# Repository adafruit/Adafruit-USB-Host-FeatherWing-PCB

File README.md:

## Adafruit USB Host FeatherWing with MAX3421E PCB

<a href="http://www.adafruit.com/products/5858"><br/>
Click here to purchase one from the Adafruit shop</a>

PCB files for the Adafruit USB Host FeatherWing with MAX3421E. 

Format is EagleCAD schematic and board layout
* https://www.adafruit.com/product/5858

### Description

Lots of microcontrollers these days have USB ports on them, to program or debug, act like a keyboard or disk drive, or simply send data between a computer and your firmware. But did you know that you can also add a USB Host port? That means that your microcontroller project can have a keyboard or mouse or disk drive plugged into it - which opens up a huge ecosystem of common off-the-shelf devices that you can now integrate. The Adafruit USB Host FeatherWing makes it easy to add USB Host support, especially now that TinyUSB supports it in the Arduino library as a 'native' interface for host support. 

This Wing uses the MAX3421E - a tried and true USB Host chip. It uses SPI plus an IRQ pin to send data to just about any USB device. Note that because the chip is older, and you're limited to the SPI port speed, you're not going to get blazing 480Mbps high speed data transfer. But for basic HID interfacing, or even reading/writing to a Mass Storage device, it does work quite well. There's a famous USB Host Library that can be used, and it's specialty is AVR support, but also seems to support nRF52 and ESP32. We personally recommend using the TinyUSB Arduino library - however the trade-off is that the chip must have TinyUSB support already which means it's great for RP2040, ESP32-S2 or S3, nRF52840, SAMD21/51 chips. Between the two libraries, just make sure your desired Feather mainboard is supported before purchasing! 

Next to the MAX3421E we have a 5V 1A booster with 500mA fuse, which can provide a nice clean 5V from the USB or Battery power supply. An enable pin is available to power cycle when desired.

Comes as an assembled Wing with some header. Solder on the header and plug into a Feather Mainboard to expand it's capabilities! Don't forget, you need driver support for the MAX3421E (see above for chips that are known working) and unless you're using a generic mouse, keyboard, CDC serial or USB mass storage device you will also need a USB driver that knows how to talk to the device - and writing a driver is non-trivial.

### License

Adafruit invests time and resources providing this open source design, please support Adafruit and open-source hardware by purchasing products from [Adafruit](https://www.adafruit.com)!

Designed by Limor Fried/Ladyada for Adafruit Industries.

Creative Commons Attribution/Share-Alike, all text above must be included in any redistribution. 
See license.txt for additional details.

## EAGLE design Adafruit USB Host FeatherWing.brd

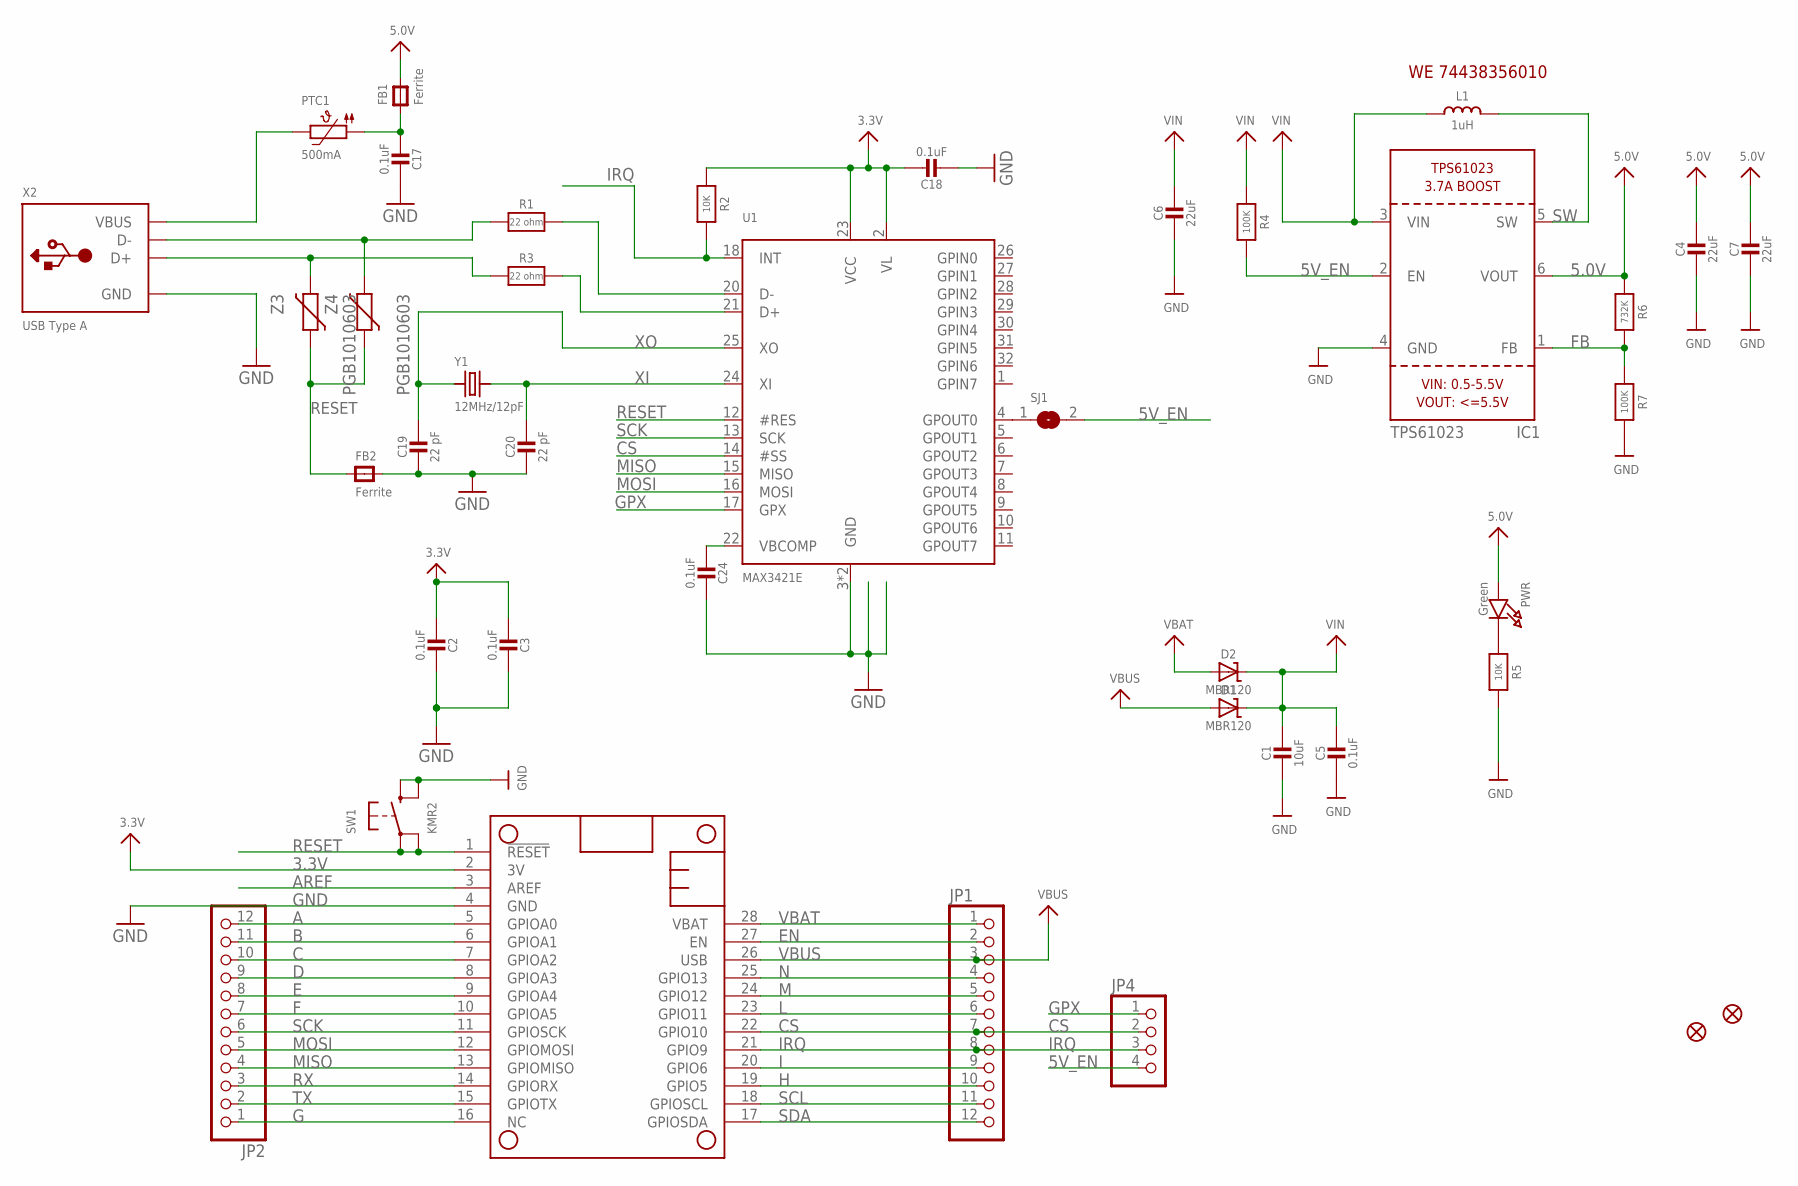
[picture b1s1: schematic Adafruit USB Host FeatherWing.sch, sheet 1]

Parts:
C1: 10uF; 0805-NO
C2, C3, C5, C17, C18, C24: 0.1uF; 0603-NO
C4, C6, C7: 22uF; 0805-NO
C19, C20: 22 pF; 0603-NO
D1, D2: MBR120; SOD-123
FB1, FB2: Ferrite; 0805-NO
FID1, FID2: FIDUCIAL_1MM
IC1: TPS61023; SOT563
JP1: HEADER-1X12; 1X12_ROUND
JP2: HEADER-1X1276MIL; 1X12_ROUND_76MIL
JP4: HEADER-1X4ROUND; 1X04_ROUND
L1: 1uH; INDUCTOR_5045_SMALLTABS
MS1: FEATHERWING_NODIM
PTC1: 500mA; 0805-NO
PWR: Green; CHIPLED_0603_NOOUTLINE
R1, R3: 22 ohm; 0603-NO
R2, R5: 10K; 0603-NO
R4, R7: 100K; 0603-NO
R6: 732K; 0603-NO
SJ1: SOLDERJUMPER; SOLDERJUMPER_ARROW_NOPASTE
SW1: KMR2; BTN_KMR2_4.6X2.8
U1: MAX3421E; PQFP32_5X5MM
X2: USB Type A; USB_HOST-SMT
Y1: 12MHz/12pF; CRYSTAL_2.5X2
Z3, Z4: PGB1010603; CT/CN0603

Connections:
3.3V: C2.1, C3.1, C18.1, MS1.2 (3V), R2.1, U1.2 (VL), U1.23 (VCC)
5.0V: C4.1, C7.1, FB1.2, IC1.6 (VOUT), PWR.A, R6.1
5V_EN: IC1.2 (EN), JP4.4, R4.2, SJ1.2
A: JP2.12, MS1.5 (GPIOA0)
AREF: MS1.3 (AREF)
B: JP2.11, MS1.6 (GPIOA1)
C: JP2.10, MS1.7 (GPIOA2)
CS: JP1.7, JP4.2, MS1.22 (GPIO10), U1.14 (#SS)
D: JP2.9, MS1.8 (GPIOA3)
E: JP2.8, MS1.9 (GPIOA4)
EN: JP1.2, MS1.27 (EN)
F: JP2.7, MS1.10 (GPIOA5)
FB: IC1.1 (FB), R6.2, R7.1
G: JP2.1, MS1.16 (NC)
GND: C1.2, C2.2, C3.2, C4.2, C5.2, C6.2, C7.2, C17.2, C18.2, C19.1, C20.1, C24.2, FB2.2, IC1.4 (GND), MS1.4 (GND), R5.2, R7.2, SW1.B (S), SW1.B' (S1), U1.3 (GND), U1.19 (GND), X2.GND
GPX: JP4.1, U1.17 (GPX)
H: JP1.10, MS1.19 (GPIO5)
I: JP1.9, MS1.20 (GPIO6)
IRQ: JP1.8, JP4.3, MS1.21 (GPIO9), R2.2, U1.18 (INT)
L: JP1.6, MS1.23 (GPIO11)
M: JP1.5, MS1.24 (GPIO12)
MISO: JP2.4, MS1.13 (GPIOMISO), U1.15 (MISO)
MOSI: JP2.5, MS1.12 (GPIOMOSI), U1.16 (MOSI)
N: JP1.4, MS1.25 (GPIO13)
unnamed: C24.1, U1.22 (VBCOMP)
unnamed: SJ1.1, U1.4 (GPOUT0)
unnamed: FB2.1, Z3.1, Z4.1
unnamed: PWR.C, R5.1
unnamed: R1.1, X2.D-, Z4.2
unnamed: R3.1, X2.D+, Z3.2
unnamed: R1.2, U1.20 (D-)
unnamed: R3.2, U1.21 (D+)
unnamed: PTC1.2, X2.VBUS
unnamed: C17.1, FB1.1, PTC1.1
RESET: MS1.1 (!RESET), SW1.A, SW1.A' (P1), U1.12 (#RES)
RX: JP2.3, MS1.14 (GPIORX)
SCK: JP2.6, MS1.11 (GPIOSCK), U1.13 (SCK)
SCL: JP1.11, MS1.18 (GPIOSCL)
SDA: JP1.12, MS1.17 (GPIOSDA)
SW: IC1.5 (SW), L1.2
TX: JP2.2, MS1.15 (GPIOTX)
VBAT: D2.A, JP1.1, MS1.28 (VBAT)
VBUS: D1.A, JP1.3, MS1.26 (USB)
VIN: C1.1, C5.1, C6.1, D1.C, D2.C, IC1.3 (VIN), L1.1, R4.1
XI: C20.2, U1.24 (XI), Y1.3 (2)
XO: C19.2, U1.25 (XO), Y1.1

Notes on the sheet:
WE 74438356010

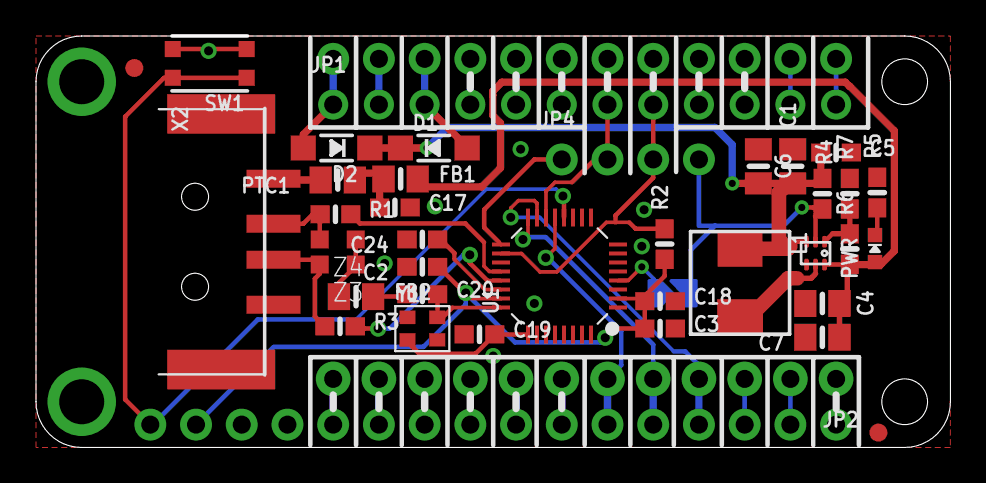
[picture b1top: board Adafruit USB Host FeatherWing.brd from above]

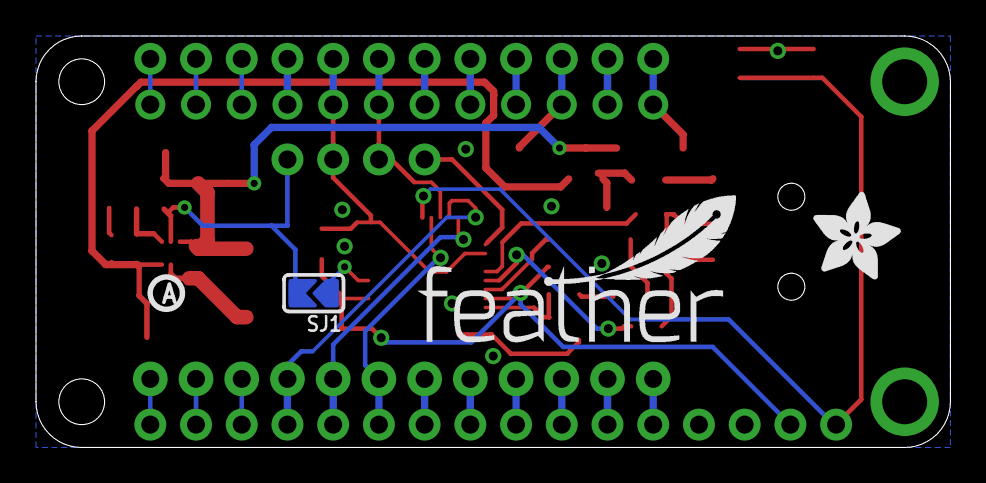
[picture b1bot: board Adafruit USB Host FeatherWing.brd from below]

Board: 2 copper layers, 50.8 x 22.9 mm, 65 parts (6 on the bottom side), 45 nets.

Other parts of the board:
PLABEL0: PLABEL0
PLABEL1: PLABEL1
PLABEL2: PLABEL2
PLABEL3: PLABEL3
PLABEL4: PLABEL4
PLABEL5: PLABEL5
PLABEL6: PLABEL6
PLABEL7: PLABEL7
PLABEL8: PLABEL8
PLABEL9: PLABEL9
PLABEL10: PLABEL10
PLABEL11: PLABEL11
PLABEL12: PLABEL12
PLABEL13: PLABEL13
PLABEL14: PLABEL14
PLABEL15: PLABEL15
PLABEL16: PLABEL16
PLABEL17: PLABEL17
PLABEL18: PLABEL18
PLABEL19: PLABEL19
PLABEL20: PLABEL20
PLABEL21: PLABEL21
U$20: FEATHERLOGO_MED
U$22: ADAFRUIT_5MM
U$26: PCBFEAT-REV-040

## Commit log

2023-12-14 cookiecutter output
